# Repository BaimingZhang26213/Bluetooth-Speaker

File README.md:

# Bluetooth-Speaker
PCB Design
# Block Diagram

Implement a PCB of BM64 (Bluetooth module) with a 24-bit high-resolution 96 kHz signal in I2S audio data format. 

PCB of ES9018K2M (DAC) with a 20-bit signal and 96dB SNR. 

PCB of LP filter with the cutoff frequency at 55 Hz, as a reference the human hearing starts at 20 Hz.

PCB of YDA138-E as a D-type amplifier to supply 10W to the speaker. 

PCB of a 15V to 5V regulator by LM317.

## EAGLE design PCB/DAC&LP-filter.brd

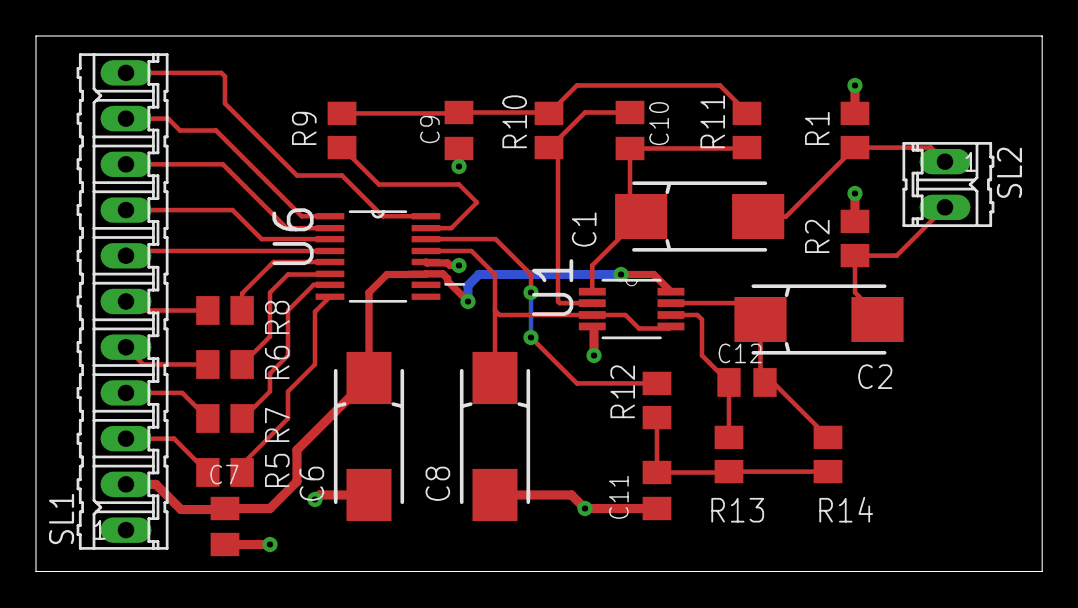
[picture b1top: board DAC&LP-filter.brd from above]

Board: 2 copper layers, 55.9 x 29.8 mm, 25 parts (0 on the bottom side), 26 nets.

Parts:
C1, C2, C6, C8: 10µ; 085CS_1AR
C7: 0.1µ; C0805K
C9, C11: 2.7n; C0805K
C10, C12: 330p; C0805K
R1, R2: 2k; M0805
R5, R6, R7, R8: 100; M0805
R9, R11, R12, R14: 3.9k; M0805
R10, R13: 12k; M0805
SL1: 11P
SL2: 02P
U1: AD8646ARMZ; SOP65P490X110-8N
U6: PCM1780DBQ; SOP63P600X175-16N

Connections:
+5V: C6.+, C7.1, SL1.2, U1.8, U6.11
AGND: C6.-, C7.2, C8.-, C9.2, C11.2, R1.1, R2.1, SL1.1, U1.4, U6.12
BCK: R7.2, SL1.4
DATA: R6.2, SL1.5
LRCK: R5.2, SL1.3
MC: SL1.8, U6.3
MD: SL1.7, U6.4
MS: SL1.9, U6.2
unnamed: C1.-, R1.2, SL2.1
unnamed: C2.+, C12.1, R14.1, U1.7
unnamed: C2.-, R2.2, SL2.2
unnamed: R5.1, U6.8
unnamed: R6.1, U6.6
unnamed: R7.1, U6.7
unnamed: R8.1, U6.5
unnamed: C8.+, U1.3, U1.5, U6.13
unnamed: R9.2, U6.15
unnamed: C9.1, R9.1, R10.2, R11.2
unnamed: C1.+, C10.1, R11.1, U1.1
unnamed: C10.2, R10.1, U1.2
unnamed: R12.2, U6.14
unnamed: C11.1, R12.1, R13.2, R14.2
unnamed: C12.2, R13.1, U1.6
SCK: R8.2, SL1.6
ZEROL/NA: SL1.10, U6.1
ZEROR/ZEROA: SL1.11, U6.16

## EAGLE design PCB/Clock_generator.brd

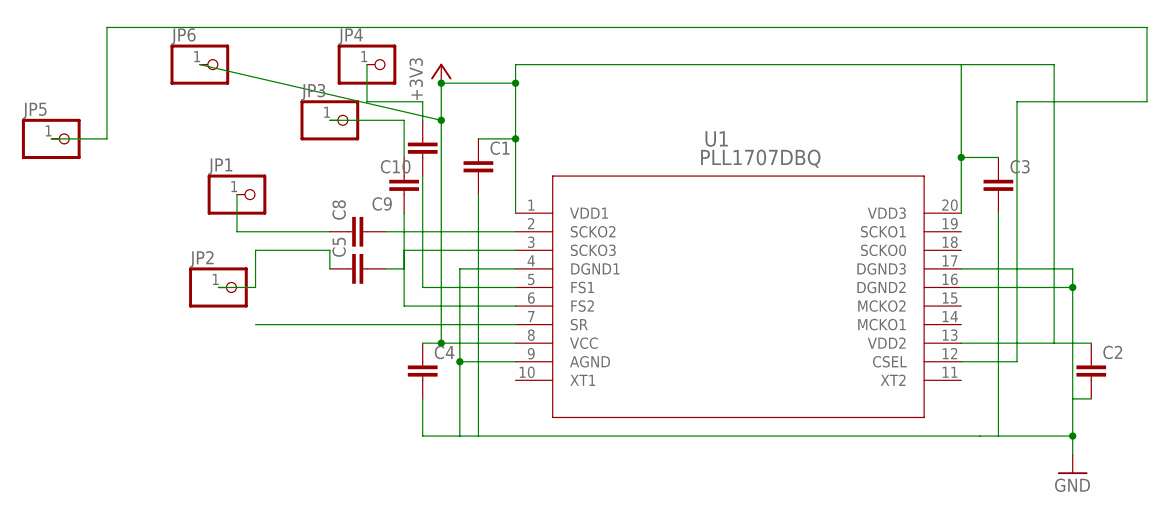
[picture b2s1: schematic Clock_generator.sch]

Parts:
C1, C2, C3, C4, C5, C8, C9, C10: C-EUC0805K; C0805K
JP1, JP2, JP3, JP4, JP5, JP6: PINHD-1X1; 1X01
U1: PLL1707DBQ; DBQ20

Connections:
+3V3: C1.1, C2.1, C3.1, C4.1, JP6.1, U1.1 (VDD1), U1.8 (VCC), U1.13 (VDD2), U1.20 (VDD3)
GND: C1.2, C2.2, C3.2, C4.2, U1.4 (DGND1), U1.9 (AGND), U1.16 (DGND2), U1.17 (DGND3)
unnamed: C8.2, U1.2 (SCKO2)
unnamed: C5.2, U1.3 (SCKO3)
unnamed: C8.1, JP1.1
unnamed: C5.1, JP2.1
unnamed: C10.1, U1.5 (FS1)
unnamed: C9.1, U1.6 (FS2)
unnamed: JP5.1, U1.12 (CSEL)
unnamed: C9.2, JP3.1
unnamed: C10.2, JP4.1

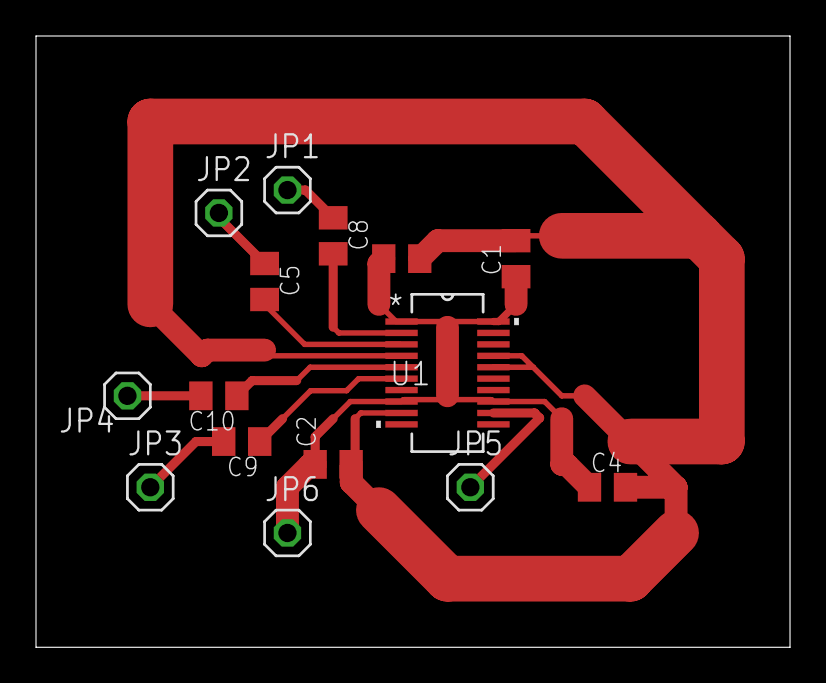
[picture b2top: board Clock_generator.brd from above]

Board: 2 copper layers, 41.9 x 34.0 mm, 15 parts (0 on the bottom side), 11 nets.

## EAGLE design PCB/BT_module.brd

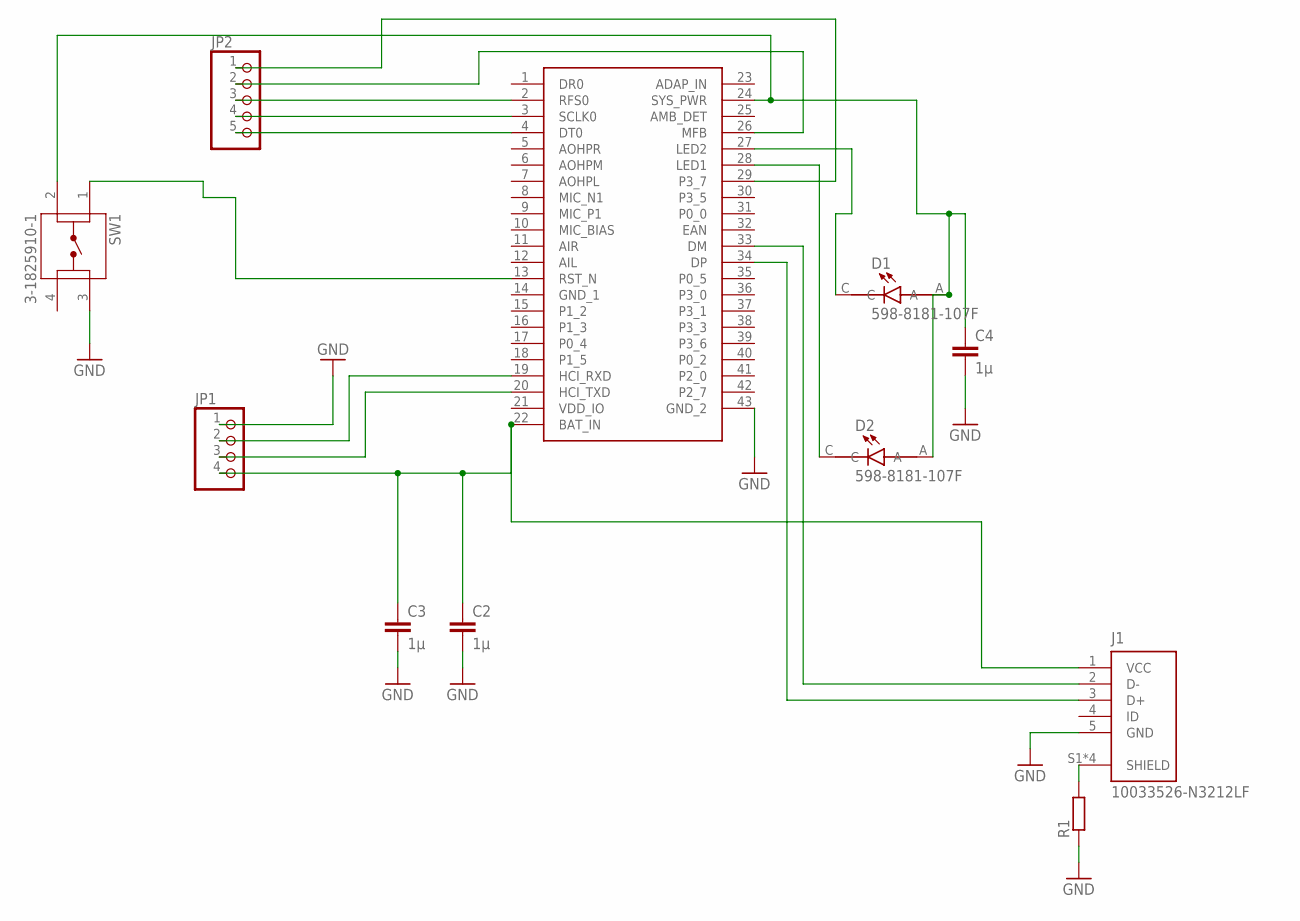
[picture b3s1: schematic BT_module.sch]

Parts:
ANT2: BM64SPKS1MC2-0001AA; BM64SPKS1MC20001AA
C2, C3, C4: 1µ; C0805
D1, D2: 598-8181-107F; LEDC2012X70N
J1: 10033526-N3212LF; AMPHENOL_10033526-N3212LF
JP1: PINHD-1X4; 1X04
JP2: PINHD-1X5; 1X05
R1: R-EU_M0805; M0805
SW1: 3-1825910-1; TE_3-1825910-1

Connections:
GND: ANT2.43 (GND_2), C2.2, C3.2, C4.2, J1.5 (GND), JP1.1, R1.1, SW1.3
unnamed: ANT2.29 (P3_7), JP2.1
unnamed: J1.S1 (SHIELD), J1.S2 (SHIELD), J1.S3 (SHIELD), J1.S4 (SHIELD), R1.2
unnamed: ANT2.27 (LED2), D1.C
unnamed: ANT2.28 (LED1), D2.C
unnamed: ANT2.24 (SYS_PWR), C4.1, D1.A, D2.A, SW1.2
unnamed: ANT2.2 (RFS0), JP2.3
unnamed: ANT2.3 (SCLK0), JP2.4
unnamed: ANT2.33 (DM), J1.2 (D-)
unnamed: ANT2.13 (RST_N), SW1.1
unnamed: ANT2.4 (DT0), JP2.5
unnamed: ANT2.22 (BAT_IN), C2.1, C3.1, J1.1 (VCC), JP1.4
unnamed: ANT2.26 (MFB), JP2.2
unnamed: ANT2.19 (HCI_RXD), JP1.2
unnamed: ANT2.20 (HCI_TXD), JP1.3
unnamed: ANT2.34 (DP), J1.3 (D+)

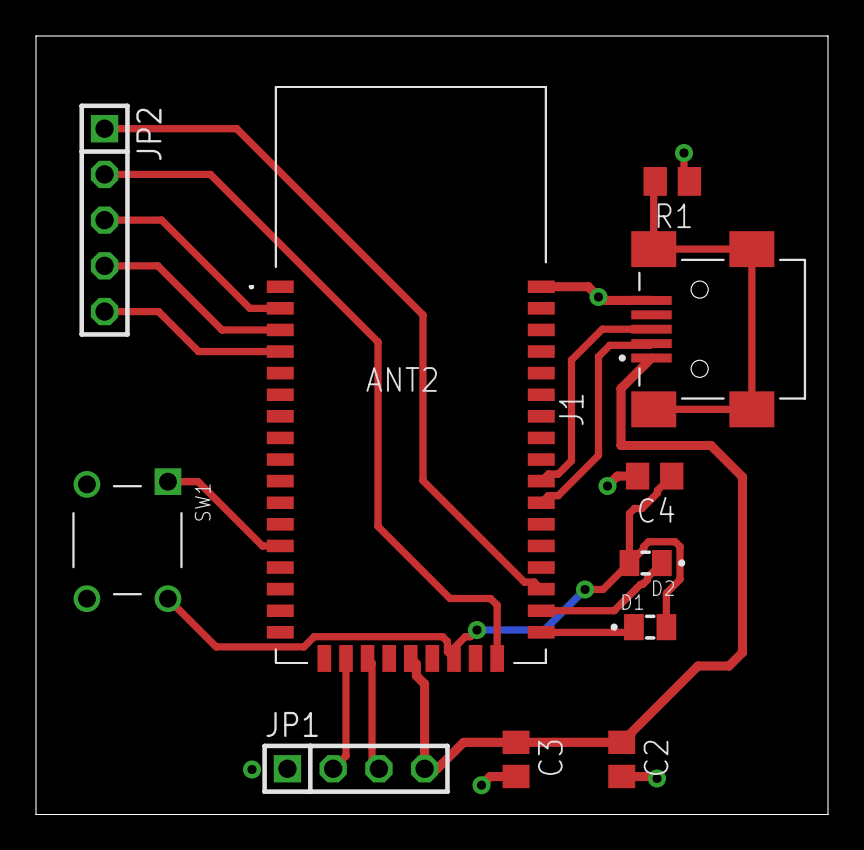
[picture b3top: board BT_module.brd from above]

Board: 2 copper layers, 44.0 x 43.2 mm, 11 parts (0 on the bottom side), 16 nets.

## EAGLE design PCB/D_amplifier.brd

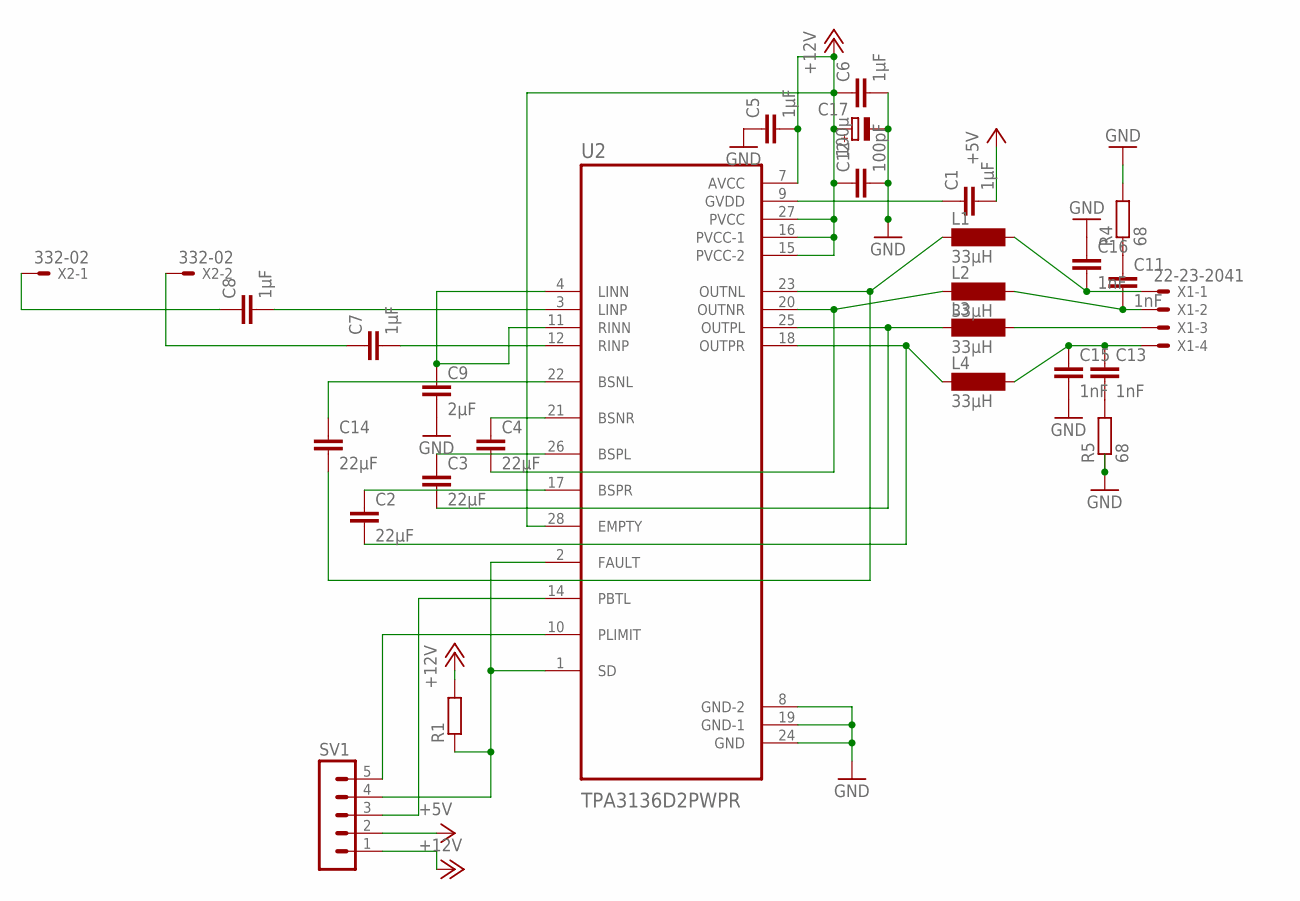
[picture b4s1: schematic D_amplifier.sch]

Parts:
C1, C5, C6, C7, C8: 1µF; C0805K
C2, C3, C4, C14: 22µF; C0805K
C9: 2µF; C0805K
C11, C13, C15, C16: 1nF; C0805K
C12: 100pF; C0805K
C17: 100µ; 085CS_1AR
L1, L2, L3, L4: 33µH; SD12-680
R1: R-EU_R0805; R0805
R4, R5: 68; M0805
SV1: MA05-1
U2: TPA3136D2PWPR; IC_TPS61196PWPRQ1
X1: 22-23-2041
X2: 332-02

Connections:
+5V: C1.2, SV1.2
+12V: C5.2, C6.1, C12.1, C17.+, R1.2, SV1.1, U2.7 (AVCC), U2.15 (PVCC-2), U2.16 (PVCC-1), U2.27 (PVCC), U2.28 (EMPTY)
GND: C5.1, C6.2, C9.2, C12.2, C15.2, C16.1, C17.-, R4.2, R5.1, U2.8 (GND-2), U2.19 (GND-1), U2.24 (GND)
unnamed: C7.2, U2.12 (RINP)
unnamed: C8.2, U2.3 (LINP)
unnamed: SV1.5, U2.10 (PLIMIT)
unnamed: C14.2, L1.1, U2.23 (OUTNL)
unnamed: C4.2, L2.1, U2.20 (OUTNR)
unnamed: C3.2, L3.1, U2.25 (OUTPL)
unnamed: C2.2, L4.1, U2.18 (OUTPR)
unnamed: R1.1, SV1.4, U2.1 (SD), U2.2 (FAULT)
unnamed: SV1.3, U2.14 (PBTL)
unnamed: C4.1, U2.21 (BSNR)
unnamed: C3.1, U2.26 (BSPL)
unnamed: C2.1, U2.17 (BSPR)
unnamed: C14.1, U2.22 (BSNL)
unnamed: C1.1, U2.9 (GVDD)
unnamed: C7.1, X2.2
unnamed: C8.1, X2.1
unnamed: C9.1, U2.4 (LINN), U2.11 (RINN)
unnamed: C16.2, L1.2, X1.1
unnamed: C11.2, L2.2, X1.2
unnamed: L3.2, X1.3
unnamed: C13.1, C15.1, L4.2, X1.4
unnamed: C13.2, R5.2
unnamed: C11.1, R4.1

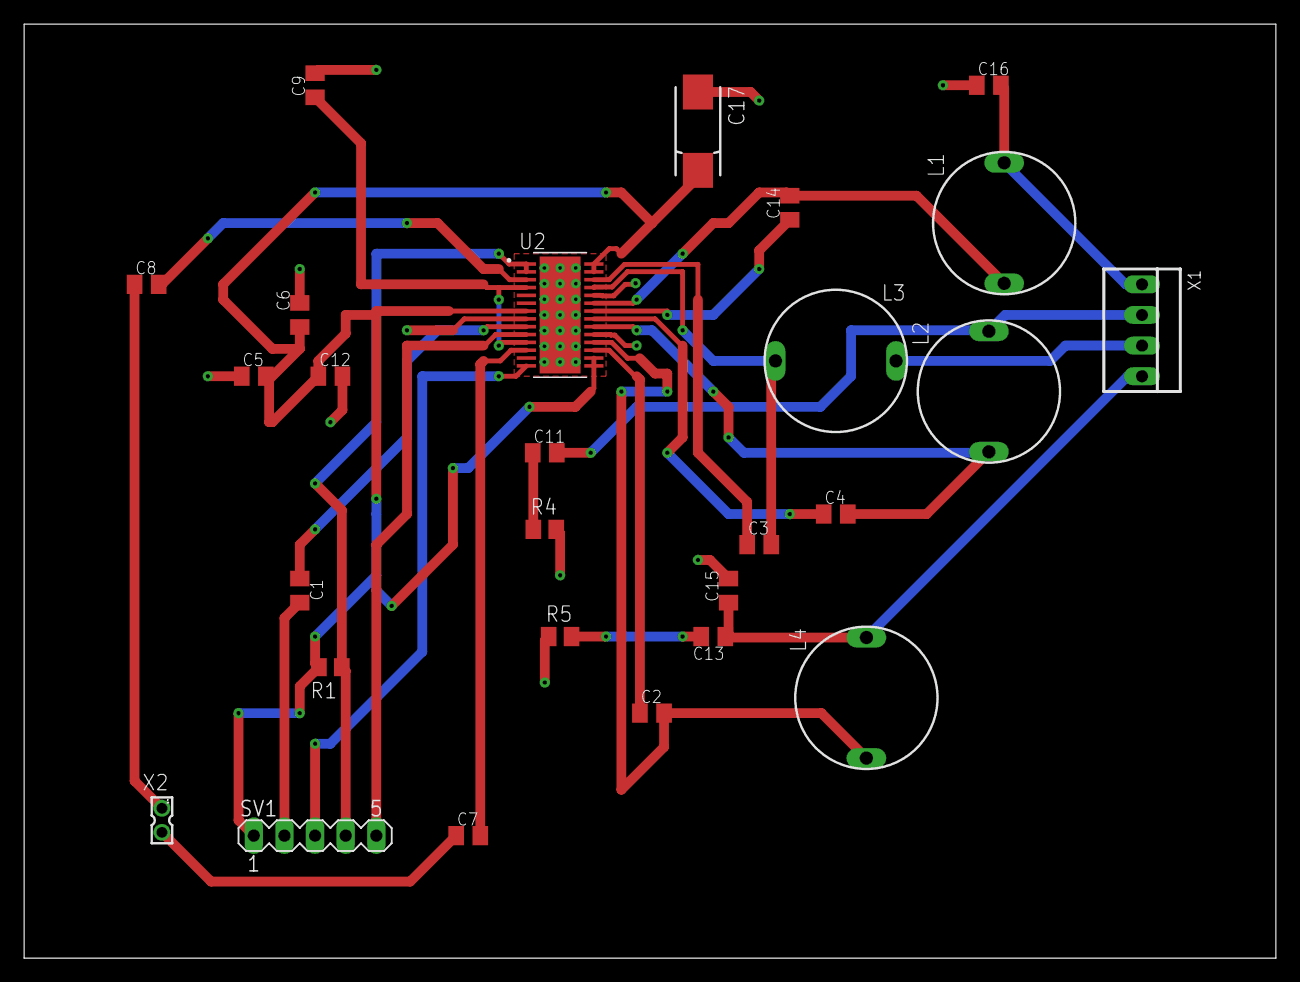
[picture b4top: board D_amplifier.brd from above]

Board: 2 copper layers, 103.8 x 77.5 mm, 27 parts (0 on the bottom side), 26 nets.

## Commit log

2021-11-29 Create 1
